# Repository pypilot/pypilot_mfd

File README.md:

This repository contains code for an open source multifunction marine display.

The data formats currently are nmea0183, signalK, and direct communication to pypilot.

It supports zeroconf (mDNS) to detect pypilot and signalk servers.   There is support for wifi, usb (serial port) and nmea0183 (rs422) communications.

The esp32s3 can drive high resolution (800x480) RGB parallel dayligth visible lcd.

A standard esp32 can be used for monochrome displays eg: jlx256160

3d printed enclosures may be waterproofed by treating (100% infill and soaking with dichtol) (FDM) or by printing with SLA/SLS.  The plexiglass cover is sealed with a rubber oring tested submerged under water for prolonged periods.

Wireless sensors are implemented specifically:
-  3d printed wind sensors using ceramic bearings and hall effect sensors (non contact)  Multiple wind sensors can be used mounted in different locations on the boat, and the sensors can compensate motion using inertial sensors.
-  pressure, humidity and air quality sensors (bme680)
-  lightning, uv and visible light sensors
-  (planned but not fully implemented)  sonar for depth, water speed, water temperature.

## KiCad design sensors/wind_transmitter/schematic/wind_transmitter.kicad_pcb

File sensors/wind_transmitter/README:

This project is for a wireless wind transmitter based on esp32

The esp32 transmits using espnow for minimal latency to a receiver (either dedicated ttgo or pypilot_mfd) on the same wireless channel.

To do OTA update, power the sensors inverted or held up side down (never occurs in normal use)

If powered normally and booted, and then inverted for 3 seconds the access point is created without code.

The access point can also be enabled later by sending an espnow message to turn it on, in this case with the wireless code.
If the code is forgotten it must be inverted to regain access.

Normally it outputs wind direction, cup rotation period (in ms) and accelerometer data.   The conversion to wind speed and direction is done by the receiver.

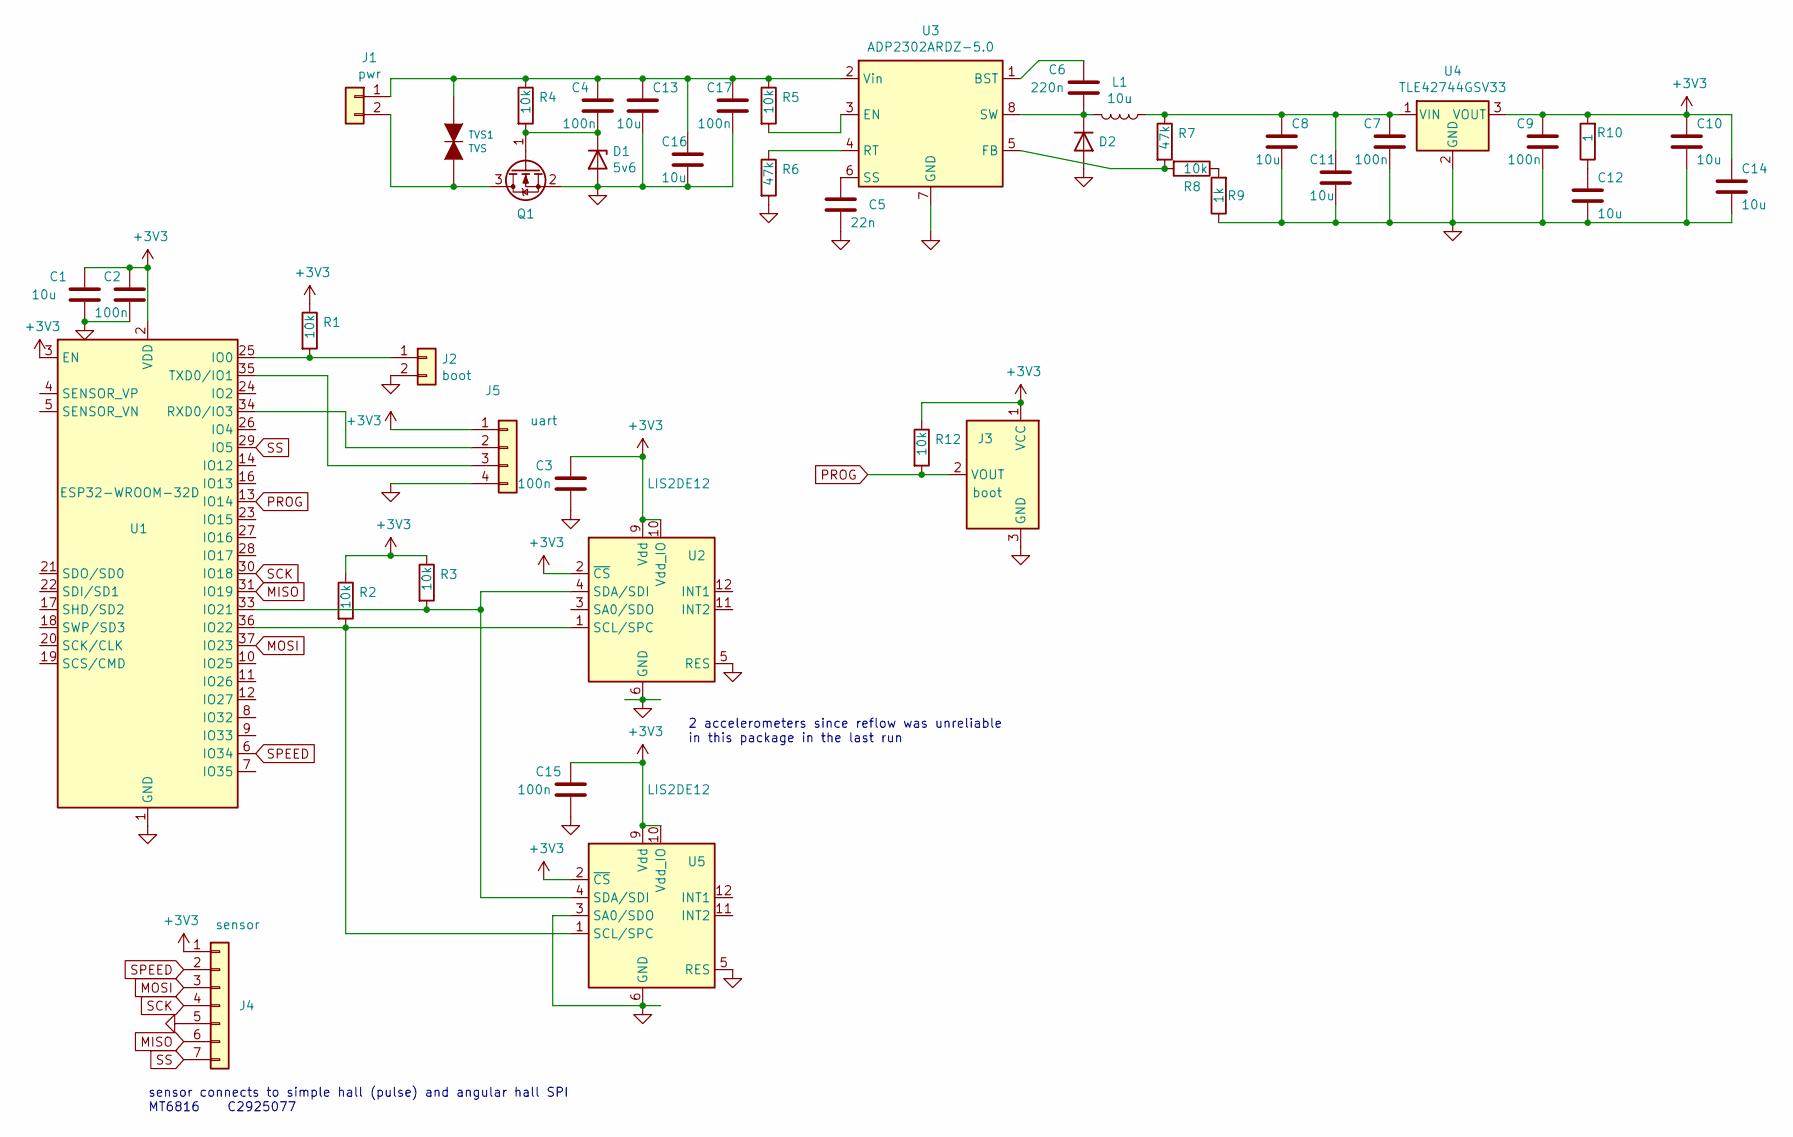
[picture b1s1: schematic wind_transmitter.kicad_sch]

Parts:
C1, C8, C10, C11, C12, C13, C14, C16: 10u; C_1206_3216Metric; LCSC C13585
C2, C3, C4, C7, C9, C15, C17: 100n; C_0805_2012Metric; LCSC C49678
C5: 22n; C_0805_2012Metric; LCSC C1729
C6: 220n; C_0805_2012Metric; LCSC C5378
D1: 5v6; D_SOD-123; LCSC C173406
D2: D; DO-214AC; LCSC C2480
J1: pwr; power_input
J2: boot; PinHeader_1x02_P2.54mm_Vertical
J3: boot; SOT-23_180; LCSC C496739
J4: sensor; PinHeader_1x07_P2.54mm_Vertical
J5: uart; JST_SH_SM04B-SRSS-TB_1x04-1MP_P1.00mm_Horizontal; LCSC C160404
L1: 10u; L_Sunlord_MWSA0518_5.4x5.2mm; LCSC C408412
Q1: Q_PMOS_GSD; SOT-23_180; LCSC C75882
R1, R2, R3, R4, R5, R8, R12: 10k; R_0805_2012Metric; LCSC C17414
R6, R7: 47k; R_0805_2012Metric; LCSC C17713
R9: 1k; R_0805_2012Metric; LCSC C17513
R10: 1; R_0805_2012Metric; LCSC C25271
TVS1: TVS; D_SOD-123F; LCSC C399267
U1: ESP32-WROOM-32D; ESP32-WROOM-32; LCSC C473012
U2, U5: LIS2DE12; LGA-12_2x2mm_P0.5mm; LCSC C189624
U3: ADP2302ARDZ-5.0; SOIC-8-1EP_3.9x4.9mm_P1.27mm_EP2.29x3mm; LCSC C187824
U4: TLE42744GSV33; SOT-223-3_TabPin2; LCSC C123093

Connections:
+3V3: C1.1, C2.1, C3.1, C9.1, C10.1, C14.1, C15.1, J3.1 (VCC), J4.1, J5.1, R1.1, R2.1, R3.1, R10.2, R12.1, U1.2 (VDD), U1.3 (EN), U2.2 (~CS), U2.9 (Vdd), U2.10 (Vdd_IO), U4.3 (VOUT), U5.2 (~CS), U5.9 (Vdd), U5.10 (Vdd_IO)
GND: C1.2, C2.2, C3.2, C5.2, C7.2, C8.2, C9.2, C10.2, C11.2, C12.2, C13.2, C14.2, C15.2, C16.2, C17.2, D1.2 (A), D2.2 (A), J2.2, J3.3 (GND), J4.5, J5.4, Q1.2 (S), R6.2, R9.1, U1.1 (GND), U1.15 (GND), U1.38 (GND), U1.39 (GND), U2.5 (RES), U2.6 (GND), U2.7 (GND), U2.8 (GND), U3.7 (GND), U4.2 (GND), U5.3 (SA0/SDO), U5.5 (RES), U5.6 (GND), U5.7 (GND), U5.8 (GND)
MISO: J4.6, U1.31 (IO19)
MOSI: J4.3, U1.37 (IO23)
unnamed: C4.2, D1.1 (K), Q1.1 (G), R4.2
unnamed: C5.1, U3.6 (SS)
unnamed: C6.1, U3.1 (BST)
unnamed: C6.2, D2.1 (K), L1.2, U3.8 (SW)
unnamed: C7.1, C8.1, C11.1, L1.1, R7.1, U4.1 (VIN)
unnamed: C12.1, R10.1
unnamed: C4.1, C13.1, C16.1, C17.1, J1.1, R4.1, R5.1, TVS1.1 (A), U3.2 (Vin)
unnamed: J1.2, Q1.3 (D), TVS1.2 (K)
unnamed: J2.1, R1.2, U1.25 (IO0)
unnamed: J5.2, U1.34 (RXD0/IO3)
unnamed: J5.3, U1.35 (TXD0/IO1)
unnamed: R2.2, U1.36 (IO22), U2.1 (SCL/SPC), U5.1 (SCL/SPC)
unnamed: R3.2, U1.33 (IO21), U2.4 (SDA/SDI), U5.4 (SDA/SDI)
unnamed: R5.2, U3.3 (EN)
unnamed: R6.1, U3.4 (RT)
unnamed: R7.2, R8.2, U3.5 (FB)
unnamed: R8.1, R9.2
PROG: J3.2 (VOUT), R12.2, U1.13 (IO14)
SCK: J4.4, U1.30 (IO18)
SPEED: J4.2, U1.6 (IO34)
SS: J4.7, U1.29 (IO5)

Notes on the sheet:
2 accelerometers since reflow was unreliable in this package in the last run
sensor connects to simple hall (pulse) and angular hall SPI MT6816 C2925077

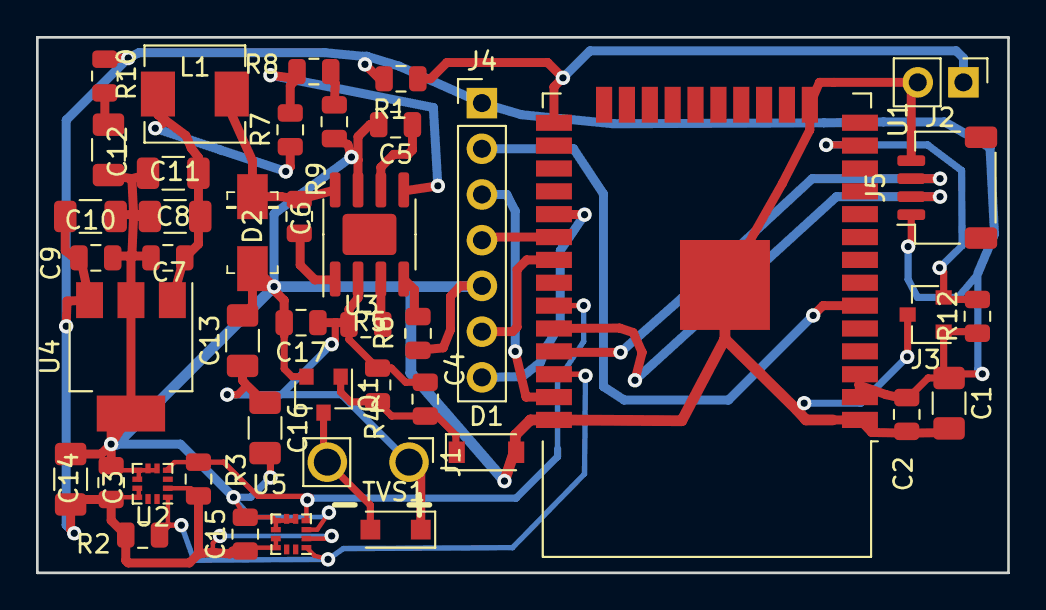
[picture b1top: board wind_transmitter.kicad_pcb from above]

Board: 2 copper layers, 53.9 x 29.7 mm, 43 parts (0 on the bottom side), 25 nets.

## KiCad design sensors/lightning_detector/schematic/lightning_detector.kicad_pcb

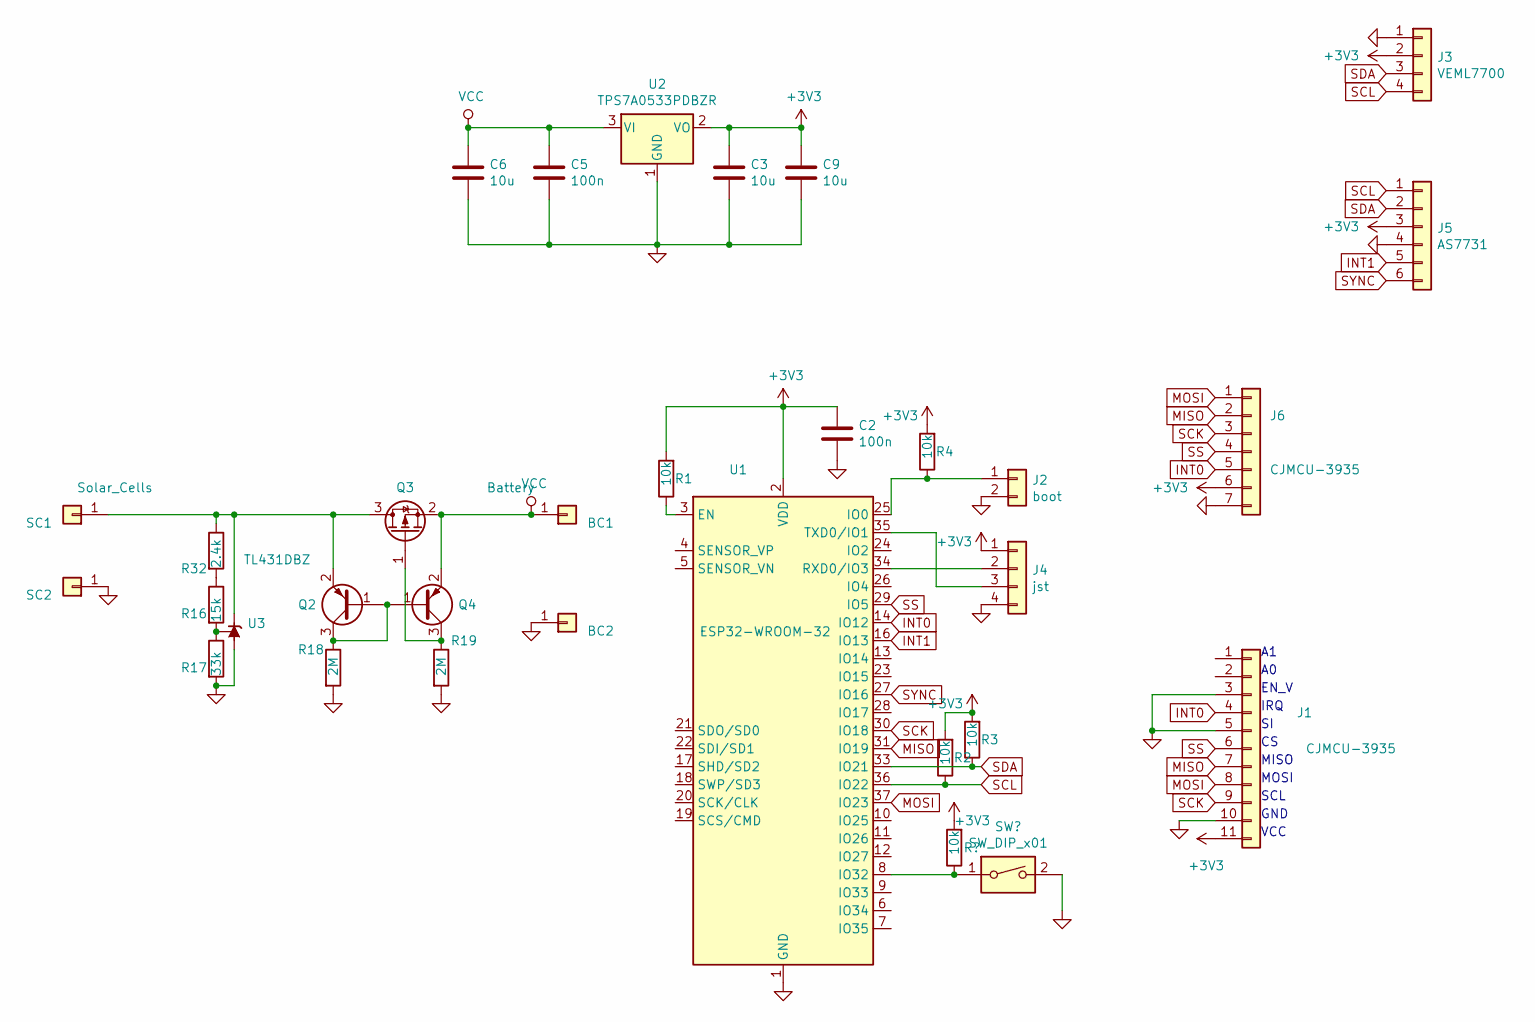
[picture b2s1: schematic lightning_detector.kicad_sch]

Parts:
BC1, BC2: Battery; Pin_D1.4mm_L8.5mm_W2.8mm_FlatFork
C2, C5: 100n; C_0805_2012Metric; LCSC C49678
C3, C6, C9: 10u; C_1206_3216Metric; LCSC C13585
J1: CJMCU-3935; PinHeader_1x11_P2.54mm_Vertical
J2: boot; PinHeader_1x02_P2.54mm_Vertical
J3: VEML7700; PinHeader_1x04_P2.54mm_Vertical
J4: jst; JST_SH_SM04B-SRSS-TB_1x04-1MP_P1.00mm_Horizontal; LCSC C160404
J5: AS7731; PinHeader_1x06_P2.54mm_Vertical
J6: CJMCU-3935; PinHeader_1x07_P2.54mm_Vertical
Q2, Q4: Q_PNP_BEC; SOT-23_180; LCSC C8543
Q3: Q_PMOS_GSD; SOT-23_180; LCSC C10487
R1, R2, R3, R4: 10k; R_0805_2012Metric; LCSC C17414
R16: 15k; R_0805_2012Metric; LCSC C17475
R17: 33k; R_0805_2012Metric; LCSC C17633
R18, R19: 2M; R_0805_2012Metric; LCSC C22976
R32: 2.4k; R_0805_2012Metric; LCSC C17526
SC1, SC2: Solar_Cells; Pin_D1.4mm_L8.5mm_W2.8mm_FlatFork
U1: ESP32-WROOM-32
U2: TPS7A0533PDBZR; SOT-23_180; LCSC C2877921
U3: TL431DBZ; SOT-23_180; LCSC C3113

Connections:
+3V3: C2.1, C3.1, C9.1, J1.11, J3.2, J4.1, J5.3, J6.6, R1.2, R2.2, R3.2, R4.2, U1.2 (VDD), U2.2 (VO)
GND: BC2.1, C2.2, C3.2, C5.2, C6.2, C9.2, J1.3, J1.5, J1.10, J2.2, J3.1, J4.4, J5.4, J6.7, R17.2, R18.2, R19.2, SC2.1, U1.1 (GND), U1.15 (GND), U1.38 (GND), U1.39 (GND), U2.1 (GND), U3.3 (A)
INT0: J1.4, J6.5, U1.14 (IO12)
INT1: J5.5, U1.16 (IO13)
MISO: J1.7, J6.2, U1.31 (IO19)
MOSI: J1.8, J6.1, U1.37 (IO23)
unnamed: J2.1, R4.1, U1.25 (IO0)
unnamed: J4.2, U1.34 (RXD0/IO3)
unnamed: J4.3, U1.35 (TXD0/IO1)
unnamed: Q2.1 (B), Q2.3 (C), Q4.1 (B), R18.1
unnamed: Q2.2 (E), Q3.3 (D), R32.1, SC1.1, U3.2 (K)
unnamed: Q3.1 (G), Q4.3 (C), R19.1
unnamed: R1.1, U1.3 (EN)
unnamed: R16.1, R32.2
unnamed: R16.2, R17.1, U3.1 (REF)
SCK: J1.9, J6.3, U1.30 (IO18)
SCL: J3.4, J5.1, R2.1, U1.36 (IO22)
SDA: J3.3, J5.2, R3.1, U1.33 (IO21)
SS: J1.6, J6.4, U1.29 (IO5)
SYNC: J5.6, U1.27 (IO16)
VCC: BC1.1, C5.1, C6.1, Q3.2 (S), Q4.2 (E), U2.3 (VI)

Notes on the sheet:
EN_V
IRQ
SCL
MOSI
GND
VCC
MISO

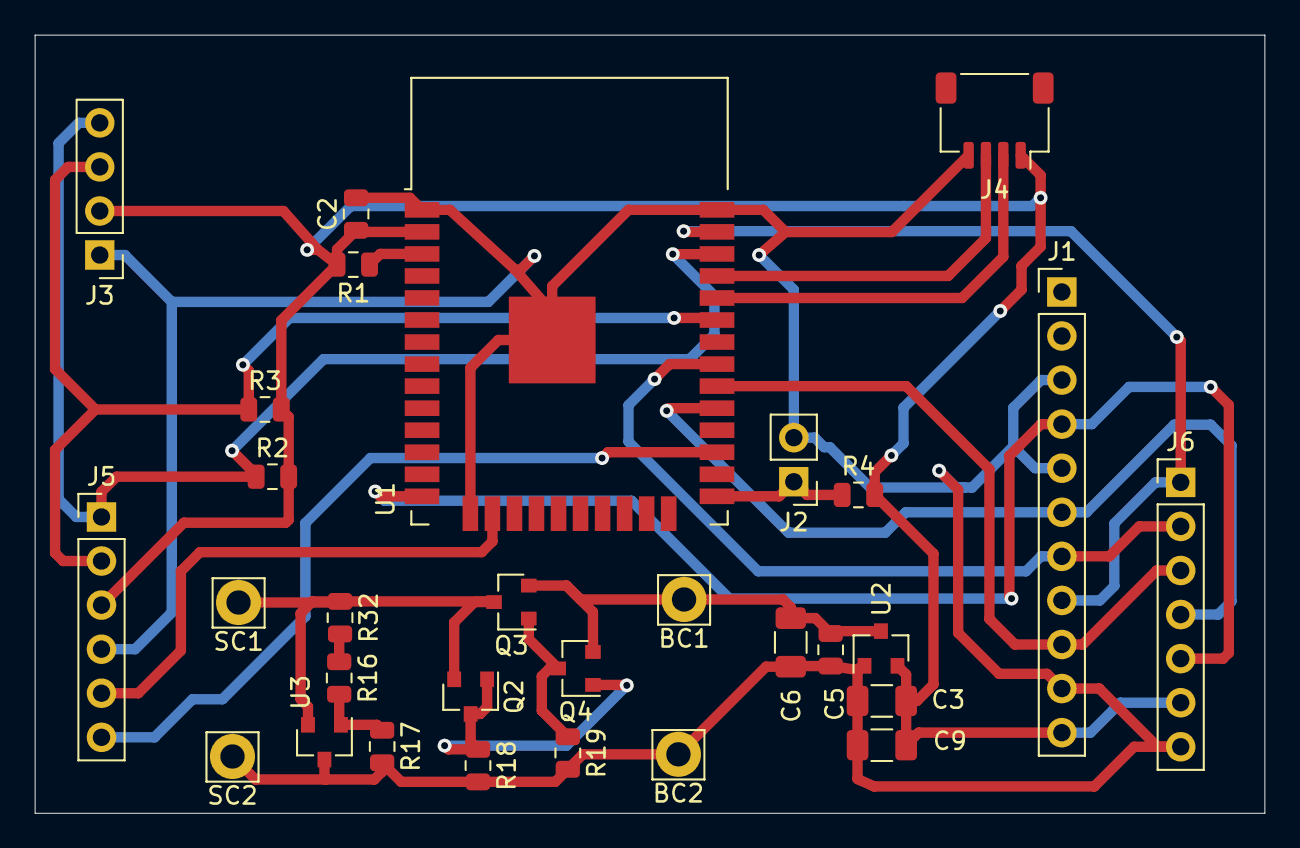
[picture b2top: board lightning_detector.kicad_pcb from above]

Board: 2 copper layers, 70.9 x 44.9 mm, 30 parts (0 on the bottom side), 21 nets.

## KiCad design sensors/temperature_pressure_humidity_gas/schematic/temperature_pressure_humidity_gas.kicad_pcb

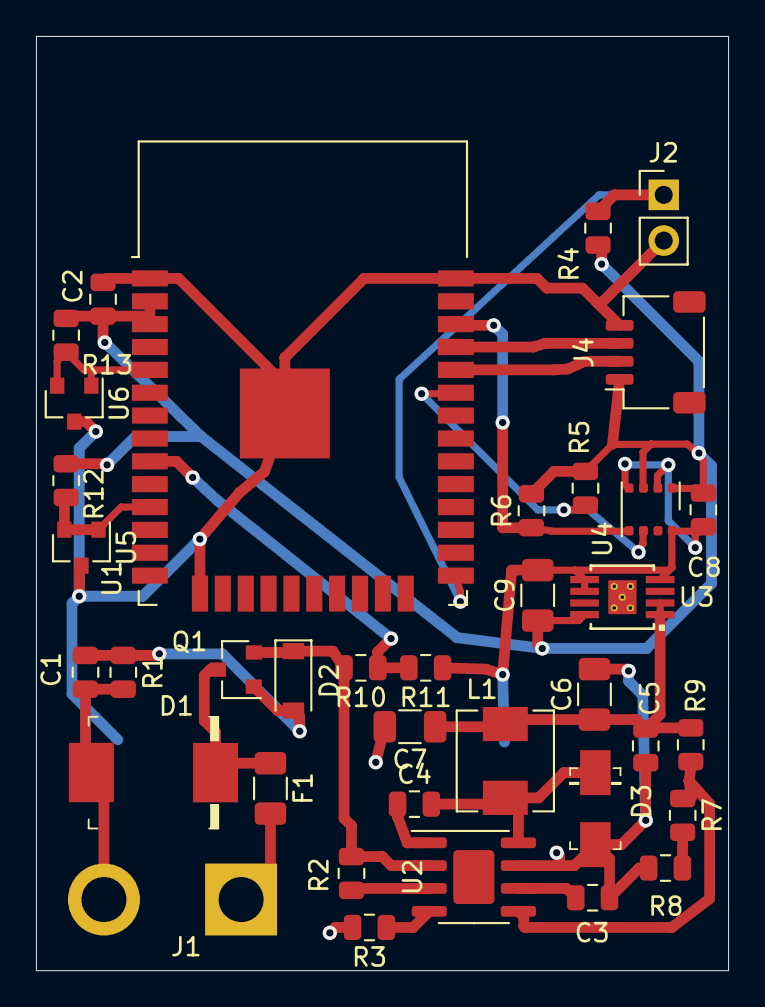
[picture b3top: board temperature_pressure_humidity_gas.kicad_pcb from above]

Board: 2 copper layers, 38.5 x 51.9 mm, 37 parts (0 on the bottom side), 22 nets.

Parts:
C1: 1u; C_0805_2012Metric
C2, C5, C8: 100n; C_0805_2012Metric
C3: 22n; C_0805_2012Metric
C4: 220n; C_0805_2012Metric
C6, C7, C9: 10u; C_1206_3216Metric
D1: 40V; DO-214AB
D2: 5v6; D_SOD-123
D3: D; DO-214AC
F1: Fuse; Fuse_1206_3216Metric
J1: Power Input (12/24); SolderWirePad_1x02_P7.62mm_Drill2.5mm
J2: boot; PinHeader_1x02_P2.54mm_Vertical
J4: jst; JST_SH_SM04B-SRSS-TB_1x04-1MP_P1.00mm_Horizontal
L1: 10u; L_Sunlord_MWSA0518_5.4x5.2mm
Q1: Q_PMOS_GSD; SOT-23_180
R1, R4, R5, R6, R7, R11: 10k; R_0805_2012Metric
R2, R3, R9: 47k; R_0805_2012Metric
R8: 1k; R_0805_2012Metric
R10: 81k; R_0805_2012Metric
R12, R13: 15k; R_0805_2012Metric
U1: ESP32-WROOM-32
U2: ADP2303ARDZ; SOIC-8-1EP_3.9x4.9mm_P1.27mm_EP2.29x3mm
U3: TPS7133; DGN-8
U4: BME680; Bosch_LGA-8_3x3mm_P0.8mm_ClockwisePinNumbering
U5: 2.5v; SOT-23_180
U6: 1.24v; SOT-23_180

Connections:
+3V3: C2.1, C8.1, C9.1, J4.1, R4.2, R5.2, R6.2, R12.2, R13.2, U1.2, U1.3, U3.8, U4.6, U4.8
GND: C1.2, C2.2, C3.2, C5.2, C6.2, C7.2, C8.2, C9.2, D1.2, D3.2, J1.2, J2.2, J4.4, R1.2, R3.2, R8.1, R11.1, U1.1, U1.15, U1.38, U1.39, U2.7, U3.4, U3.5, U3.6, U4.1, U4.5, U4.7, U5.3, U6.3
unnamed: C1.1, D2.2, Q1.1, R1.1
unnamed: C3.1, U2.6
unnamed: C4.1, U2.1
unnamed: C4.2, D3.1, L1.2, U2.8
unnamed: C5.1, C6.1, C7.1, L1.1, R9.1, U3.1, U3.2
unnamed: D1.1, F1.1, Q1.3
unnamed: F1.2, J1.1
unnamed: J2.1, R4.1, U1.25
unnamed: J4.2, U1.34
unnamed: J4.3, U1.35
unnamed: R2.2, U2.3
unnamed: R3.1, U2.4
unnamed: R7.1, R9.2, U2.5
unnamed: R7.2, R8.2
unnamed: R10.1, R11.2, U1.9
unnamed: R12.1, U1.11, U5.1, U5.2
unnamed: R13.1, U1.5, U6.1, U6.2
SCL: R6.1, U1.36, U4.4
SDA: R5.1, U1.33, U4.3
VCC: D2.1, Q1.2, R2.1, R10.2, U2.2

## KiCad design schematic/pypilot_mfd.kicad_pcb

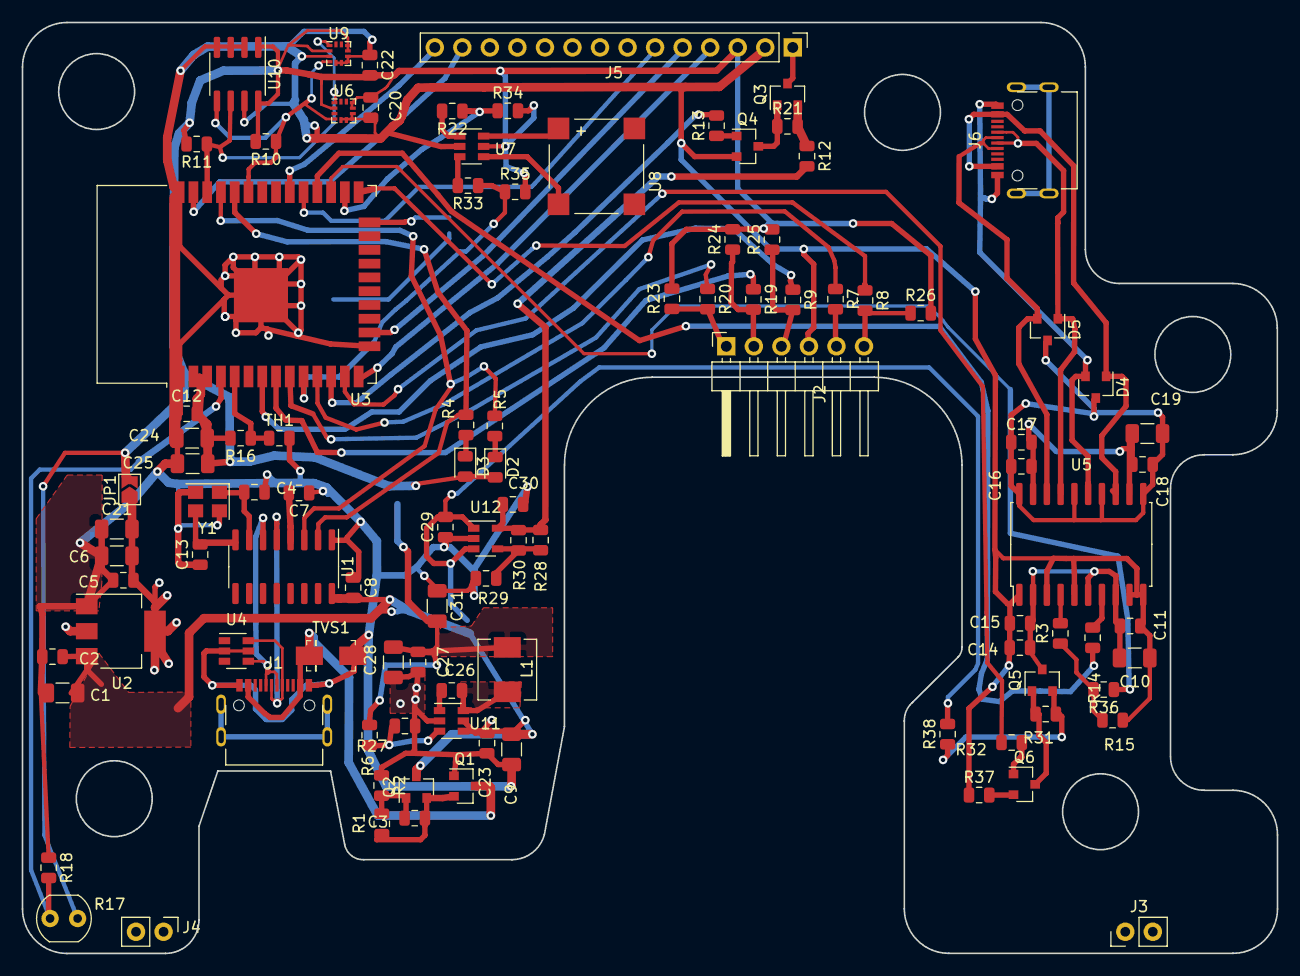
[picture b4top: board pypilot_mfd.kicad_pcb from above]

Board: 2 copper layers, 115.8 x 85.9 mm, 103 parts (1 on the bottom side), 69 nets.

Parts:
C1, C6, C9, C10, C19, C21, C24, C25, C28, C31: 10uF; C_1206_3216Metric
C2, C3, C5, C7, C8, C12, C20, C22: .1uF; C_0805_2012Metric
C4, C13: 22pF; C_0805_2012Metric
C11, C14, C17, C18, C23, C26, C27: 100n; C_0805_2012Metric
C15, C16: 10n; C_0805_2012Metric
C29, C30: 1uF; C_0805_2012Metric
D2: LED2; LED_0805_2012Metric
D3: LED3; LED_0805_2012Metric
D4, D5: SM712; SOT-23_180
J1, J6: usb; USB_C_Receptacle_Palconn_UTC16-G
J2: keypad; PinHeader_1x06_P2.54mm_Horizontal
J3, J4: Conn_01x02; PinHeader_1x02_P2.54mm_Vertical
J5: jlx256160; PinHeader_1x14_P2.54mm_Vertical
JP1, JP2: Jumper; SolderJumper-2_P1.3mm_Open_TrianglePad1.0x1.5mm
L1: 4.7uH; L_Sunlord_MWSA0518_5.4x5.2mm
Q1, Q2, Q3, Q5: Q_PMOS_GSD; SOT-23_180
Q4, Q6: Q_NMOS_GSD; SOT-23_180
R1, R21, R28, R30, R31, R34, R35: 100k; R_0805_2012Metric
R2: 20k; R_0805_2012Metric
R3, R4, R5, R8, R9, R19, R20, R22, R33, R36: 1.2k; R_0805_2012Metric
R6: 51k; R_0805_2012Metric
R7: 1k; R_0805_2012Metric
R10, R11, R13, R16, R18, R32: 10k; R_0805_2012Metric
R12: 22; R_0805_2012Metric
R14, R15: 2.4k; R_0805_2012Metric
R17: R_PHOTO; R_LDR_4.9x4.2mm_P2.54mm_Vertical
R23, R24, R25, R26: 4.7k; R_0805_2012Metric
R27, R29: 22k; R_0805_2012Metric
R37, R38: 4.7; R_0805_2012Metric
TH1: NTC; R_0805_2012Metric
TVS1: TVS; DO-214AC
U1: CH340G; SOIC-16_3.9x9.9mm_P1.27mm_90
U2: AMS1117-3.3; SOT-223-3_TabPin2_180
U3: ESP32-WROOM-32D; ESP32-WROOM-32
U4: SN65220; SOT-23-6
U5: ADM2587E; SOIC-20W_7.5x12.8mm_P1.27mm
U6, U9: LIS2DE12; LGA-12_2x2mm_P0.5mm
U7: 74AHC04; SOT-23-6_180
U8: BUZZER-freetronics_schematic; PUIAudio_SMT_0825_S_4_R_90
U10: 24LC512; SOIC-8_3.9x4.9mm_P1.27mm
U11: LMR50410; SOT-23-6_180
U12: AP2127K-ADJ; SOT-23-5
Y1: 12mhz; Crystal_SMD_3225-4Pin_3.2x2.5mm

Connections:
+3V3: C12.2, C20.2, C22.2, C24.2, C25.2, D2.2, D3.2, J5.3, JP1.2, JP2.2, R10.2, R11.2, R16.2, R17.1, R23.2, R24.2, R25.2, R26.2, R34.2, R35.2, U3.2, U3.3, U6.2, U6.9, U6.10, U7.5, U9.2, U9.9, U9.10, U10.1, U10.8
+5V: C1.2, C2.2, C8.2, C9.2, C23.2, C29.2, Q2.3, R38.2, U1.16, U2.3, U11.4, U11.5, U12.1, U12.3
BACKLIGHT: J5.1, Q3.3
BUZZERA: R22.1, R34.1, U3.26
BUZZERB: R33.1, R35.1, U3.10
CS: J5.6, U3.29
DOWN: R20.1, U3.9
GND: C1.1, C2.1, C4.1, C5.1, C6.1, C7.1, C8.1, C9.1, C10.1, C11.1, C12.1, C13.1, C14.1, C15.1, C20.1, C21.1, C22.1, C23.1, C24.1, C25.1, C27.1, C28.1, C29.1, C30.1, C31.1, J1.A1, J1.A12, J1.B1, J1.B12, J2.4, J5.2, Q1.1, Q4.2, R2.1, R15.1, R18.1, R27.2, R29.1, R37.1, TH1.2, TVS1.2, U1.1, U2.1, U3.1, U3.15, U3.38, U3.39, U4.2, U4.5, U5.1, U5.3, U5.5, U5.9, U5.10, U6.5, U6.6, U6.7, U6.8, U7.2, U9.3, U9.5, U9.6, U9.7, U9.8, U10.2, U10.3, U10.4, U10.7, U11.2, U12.2, Y1.2, Y1.4
LEDA: R13.2, U3.12
MODE: R19.1, U3.8
MOSI: J5.13, U3.37
unnamed: C3.1, Q2.1, R1.1, R2.2
unnamed: C3.2, Q1.2, Q2.2, R1.2
unnamed: C4.2, U1.7, Y1.1
unnamed: C7.2, U1.4
unnamed: C10.2, C11.2, C14.2, C15.2, Q5.3, U5.2, U5.6, U5.8
unnamed: C13.2, U1.8, Y1.3
unnamed: C16.1, C17.1, C18.1, C19.1, D4.3, D5.3, U5.11, U5.14, U5.16, U5.20
unnamed: C16.2, C17.2, C18.2, C19.2, U5.12, U5.19
unnamed: C5.2, C6.2, C21.2, JP1.1, U2.2
unnamed: C26.1, L1.1, U11.6
unnamed: C26.2, U11.1
unnamed: C27.2, C28.2, C31.2, JP2.1, L1.2, R6.1
unnamed: C30.2, R12.2, R28.2, R30.2, U12.5
unnamed: D2.1, R5.2
unnamed: D3.1, R4.2
unnamed: D4.1, J6.A4, J6.A9, J6.B4, J6.B9, U5.13
unnamed: D4.2, J6.A1, J6.A12, J6.B1, J6.B12, U5.15
unnamed: D5.1, J6.A6, J6.B6, U5.17
unnamed: D5.2, J6.A7, J6.B7, U5.18
unnamed: J1.A4, J1.A9, J1.B4, J1.B9, Q1.3, TVS1.1
unnamed: J1.A6, J1.B6, U1.5, U4.6
unnamed: J1.A7, J1.B7, U1.6, U4.4
unnamed: J2.1, R20.2, R23.1
unnamed: J2.2, R19.2, R24.1
unnamed: J2.3, R9.2, R25.1
unnamed: J2.5, R7.2
unnamed: J2.6, R8.2, R26.1
unnamed: Q3.1, Q4.3, R21.1
unnamed: Q3.2, R12.1, R21.2
unnamed: Q4.1, R13.1
unnamed: Q5.1, Q6.3, R31.1
unnamed: Q5.2, R31.2, R38.1
unnamed: Q6.1, R32.2
unnamed: Q6.2, R37.2
unnamed: R3.2, U5.4
unnamed: R14.2, U5.7
unnamed: R3.1, R15.2, R36.2
unnamed: R16.1, TH1.1, U3.5
unnamed: R17.2, R18.2, U3.4
unnamed: R22.2, U7.1
unnamed: R6.2, R27.1, U11.3
unnamed: R28.1, R29.2, R30.1, U12.4
unnamed: R33.2, U7.3
unnamed: U7.4, U8.2
unnamed: U7.6, U8.1
PWR: R8.1, U3.25
PWR_LED: R7.1, U3.11
RS: J5.4, U3.14
RS422_PWR: R32.1, U3.13
RST: J5.5, U3.16
RX: R4.1, U1.2, U3.34
RX2: R36.1, U3.27
SCK: J5.14, U3.30
SCL: R11.1, U3.36, U6.1, U9.1, U10.6
SDA: R10.1, U3.33, U6.4, U9.4, U10.5
TX: R5.1, U1.3, U3.35
TX2: R14.1, U3.28
UP: R9.1, U3.7

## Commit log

2024-03-29 tested support for signalk working
2024-03-30 a few updates
2024-03-31 more updates!
2024-04-01 more updates
2024-04-04 continuing initial development
2024-04-19 improvements, ais plotting working
2024-04-21 update data display
2024-05-23 improve enclosure
2024-05-23 update schematic and code fixes
2024-06-03 update schematics
2024-06-05 update schematic and enclosure
2024-06-07 support rotation and mirroring
2024-06-23 updates to enclosure
2024-06-23 update schematic
2024-07-03 many updates!
2024-07-03 many more updates, work in progress
2024-07-08 updates to compile with reorganization
2024-07-14 improve format
2024-07-25 update model
2024-07-25 update source code
2024-07-25 improve alarms
2024-07-26 update alarms
2024-07-27 update history and interface
2024-07-29 convert to std::string and rapidjson
2024-07-29 add cover model
2024-07-29 add calibration
2024-07-31 update history display
2024-08-02 update layout
2024-08-02 improve data organization
2024-08-02 add back enclosure
2024-08-02 remove old data files
2024-08-02 add data file script
2024-08-03 reorganize project
2024-08-04 updates to build esp-idf
2024-08-05 more updates making graphics working
2024-08-06 optimize circle rendering using compressed scanline cache
2024-08-06 optimize rotated text rendering
2024-08-07 improvements to make color screen working
2024-08-08 update for both esp32 and esp32s3 build
2024-08-09 additional work to update web interfaces
2024-08-13 update display and history
2024-08-13 add history css
2024-08-13 add schematics and models for sensors
2024-08-13 add gitignore files
2024-08-13 add more files
2024-08-13 add color enclosure
2024-08-13 add wind transmitter
2024-08-14 compiling wind transmitter without arduino dependencies
2024-08-14 improve poweroff abilities
2024-08-16 updates to draw less power, sleeping at 100uA
2024-08-17 update display
2024-08-21 update drivers and build
2024-08-25 many improvements to rendering and data handling
2024-08-25 add lightning detector
2024-08-26 update enclosures and schematics
2024-09-03 add foot prints
2024-09-10 update enclosure
2024-09-29 many updates
2024-10-06 update enclosure/schematic
2025-09-17 update schematic for esp32s3
2025-09-17 update sensor schematics
2025-09-17 reorganize graphics driver and add buzzer volume setting
2025-09-19 improve buzzer volume and support 2bpp 4 gray for cog module
2025-09-29 improve rendering
2026-03-07 add receiver using ttgo
2026-03-17 improve sensors, adding web config for wind transmitter
2026-03-17 add readme
2026-03-19 improve web/settings
2026-03-19 add missing files and update gitignore
2026-03-22 fix settings and other issues
2026-03-22 improve serial command interface
2026-03-22 fix unlocking
2026-03-22 slight improvements
2026-03-23 add wifi statistics
2026-03-23 update models
